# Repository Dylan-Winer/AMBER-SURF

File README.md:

# AMBER-SURF
Repository hosting project files as part of my Summer Undergraduate Research Fellowship (SURF) 2025 project within the AMBER Lab at Caltech.

## Mechanical Components & Assembly

This section covers the physical build of the foot modules and begins exactly where the right-foot assembly was left off.

---

### Complete the Right Foot: Rubber Sole & Adhesive Nuts

1. **Get the sole DXF**
   - Download `sole_base.DXF` from this repo:  
     https://github.com/Dylan-Winer/AMBER-SURF/blob/main/SolidWorks-CAD/G1_Integration/DXF_G1_3/sole_base.DXF

2. **Cut the rubber sole**
   - Acquire **1/8" thick rubber** sheet.
   - **Waterjet** cut the sole using `sole_base.DXF`. Deburr/trim if needed for a clean perimeter.

3. **Bolt the remaining hardware**
   - From the bag labeled **“4/40 BOLTS & SPACERS”**, locate the **four remaining adhesive nuts**, **4-40 bolts**, and **spacers**.
   - Install these in the positions on the **right foot** where bolts are currently missing. Snug the 4-40 bolts; don’t over-torque.
   - There are through-holes cut into the cable channels on both the heel connectors. Use these to fit an allen key through. You may need to push the cables out of the way with the allen key.

4. **Bond the adhesive nuts to the rubber**
   - Remove the rubber sole; place a small, even bead of **Gorilla Glue** *or* a suitable **epoxy** on the **underside of all 8 adhesive nuts**.
   - Press the **waterjet rubber sole** onto the adhesive nuts with **even pressure**. Using a **vise** to hold the foot makes this easier; protect surfaces with scrap pads.
   - **Cure per adhesive instructions.** (If using Gorilla Glue, lightly dampen the rubber for proper foaming; for epoxy, degrease both surfaces first.)

5. **Prep for base plate + toe installation**
   - **Unscrew** the four **4-40 bolts & spacers** that mount the **heel connector** to the foot so the **right foot matches the left**.
   - The **heel must come off** so the **base plate and toe** can be **slid on from the front**.

> ✅ Quick checklist  
> - [ ] Rubber sole waterjet and is clean  
> - [ ] All 8 adhesive nuts bonded and cured  
> - [ ] Heel connector hardware removed (right foot)  
> - [ ] Fit check: base plate + toe can slide on from the front

---

### Install Each Module (Left & Right Feet)

1. **Slide-on fit**
   - **Slip the G1 foot** through the **toe cover** until the bottom of the G1 foot is **fully seated** on the **top of the bottom base plate**.
   - Verify the **toe and heel bumpers** **fully enclose** the foot with uniform contact.

2. **Reinstall heel hardware**
   - Cover the heel of the G1 with the **heel mounts**.
   - **Screw the four 4-40 bolts + spacers** into the **four heel-mount holes**. Tighten evenly in a cross pattern until snug.

3. **Cable & strain relief**
   - Route cables cleanly along edges and through any provided channels. Add **strain relief** (zip ties/adhesive anchors) to protect connectors and solder joints.

4. **USB to host**
   - Connect **micro-USB** from **each foot module** to the computer. In practice you’ll likely use **USB extension cables** plus **90° micro-USB cables** to keep a low profile.

5. **Proceed to logging**
   - Follow the **Arduino/CoolTerm** instructions in the previous section to set **per-foot baud rates** and **capture data**.

# AMBER Lab SURF 2025 — G1 Foot Sensing Module

High-rate (1000 Hz) force + IMU logging for the Unitree G1 humanoid foot.  
The following contains Teensy 4.1 usage notes to capture synchronized FSR forces and MPU-6050 orientation/gyro data to CSV via CoolTerm.

---

## TL;DR (How to run & log)

1. **Install & open CoolTerm.**
2. **Connect the Teensy (USB).**
3. In CoolTerm: **Connection → Options…**
   - **Port:** select the COM port associated with your Teensy.
   - **Baudrate:** set to the same value used in firmware `Serial.begin(BAUDRATE)` (defaults shown in the code below are `2,000,000`).
   - Click **OK**.
4. Click **Connect**.
5. Start file logging: **Connection → File Capture → Start…**
   - Choose a folder, **create/name a `.txt` file**, click **Save**.
6. In the CoolTerm terminal, press **`s`** to **start** the program (CSV header prints once).
7. **Run your G1 test** (walk/stance as needed).
8. Press **`x`** to **stop** the program.
9. Stop file logging: **Connection → File Capture → Stop**.

> **Left vs Right foot**  
> You will run **two Teensies** (left/right) at **different baud rates** to avoid USB bandwidth contention and to keep ports distinct.  
> - Edit `Serial.begin(BAUDRATE)` in each foot’s firmware (e.g., Left `2,000,000`, Right `1,500,000`).  
> - In CoolTerm, pick the matching COM port and set the **Baudrate** accordingly for each run.

---

## Data format (CSV columns)

When logging is active, the firmware prints:
time_s,FSR1_N,FSR2_N,FSR3_N,FSR4_N,qw,qx,qy,qz,gx_rad_s,gy_rad_s,gz_rad_s

- **time_s** — seconds since you pressed `s`
- **FSR*_N** — force in Newtons after per-sensor linear calibration and dead-zone/zero-clipping (<2 N → 0)
- **qw..qz** — unit quaternion from Mahony filter
- **g*_rad_s** — body-frame gyro rates (rad/s) derived from RAW with offsets & scale

---

## Hardware overview

- **Controller:** Teensy 4.1 (3.3 V logic)
- **FSRs:** 4× FlexiForce A201 (per-sensor linear calibration applied)
- **IMU:** MPU-6050
- **Loop rate:** 1000 Hz fixed tick (1 ms)

---

## Build & Flash (Teensy 4.x)

1. Open this repo’s firmware in **Arduino IDE** or **Arduino CLI** with **Teensyduino** installed.
2. Select **Board: Teensy 4.0/4.1** and the correct **Port**.
3. (Optional) Adjust:
   - `Serial.begin(BAUDRATE)` for your left/right feet.
   - FSR calibration `slope[]` and `intercept[]`.
   - Mahony gains `Kp`, `Ki`.
4. **Upload**.

## 3) Analyze Data (Python)

Program link (full script):  
**➡️ https://github.com/Dylan-Winer/AMBER-SURF/blob/main/Python_Code/G1_Data_Analysis/Force_Plot_Final.py**

**Use it like this:**
- Replace `file_path` with your CoolTerm **.txt/.csv** path.
- Set `t_start_s` and `t_end_s` (easiest way to focus on a window; set `0` to analyze everything).
- Run the script to get **plots** and **replay videos** (MP4 if FFmpeg available; otherwise GIF).
- Don’t need outputs? Comment out the plot sections and/or the `make_replay_video(...)` calls.

**Expected columns** in the file:
time_s,FSR1_N,FSR2_N,FSR3_N,FSR4_N,qw,qx,qy,qz,gx_rad_s,gy_rad_s,gz_rad_s

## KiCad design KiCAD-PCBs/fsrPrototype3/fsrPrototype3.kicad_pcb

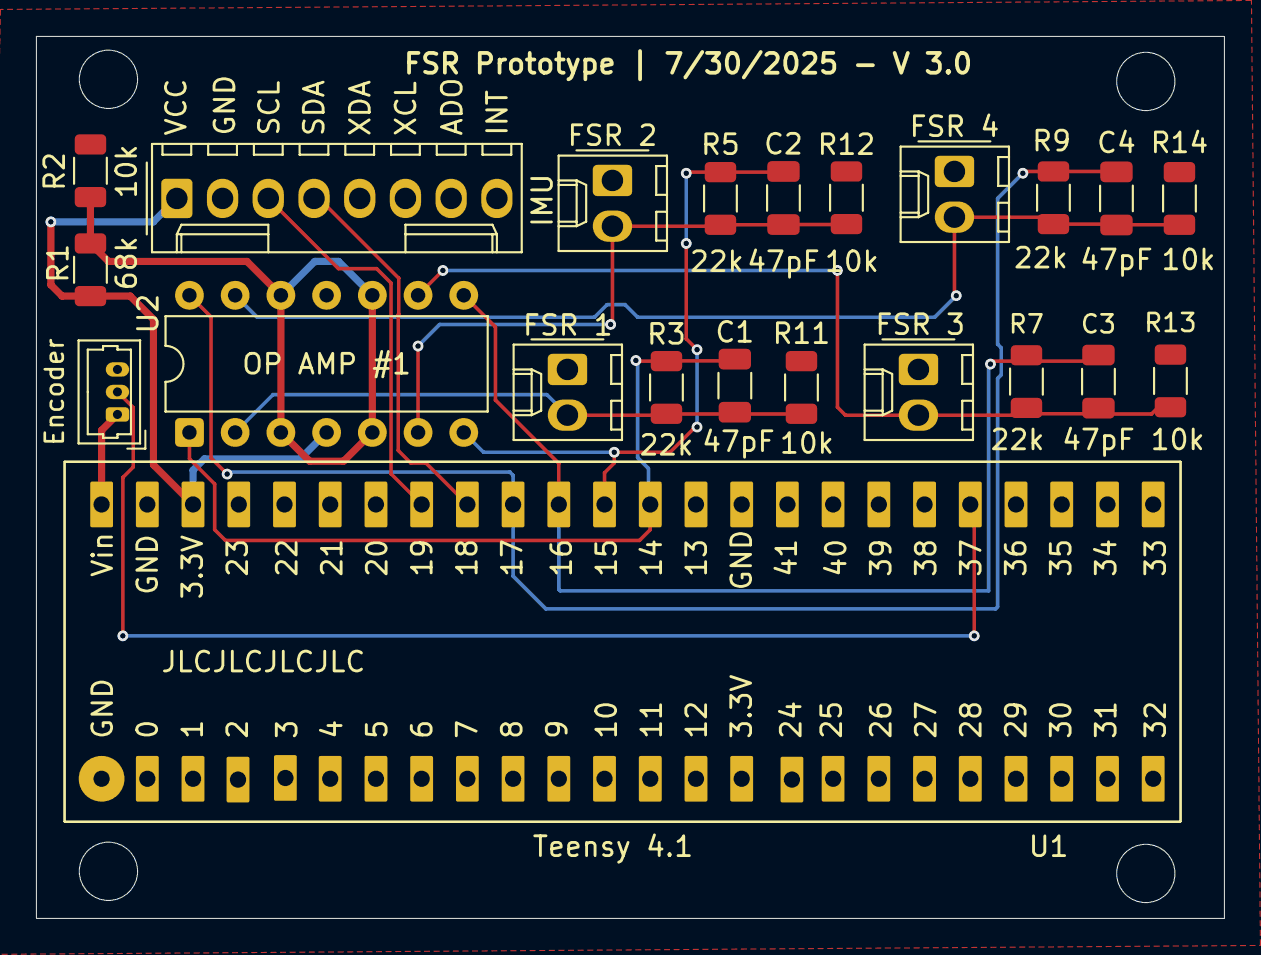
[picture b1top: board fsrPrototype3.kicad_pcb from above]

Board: 2 copper layers, 66.0 x 49.0 mm, 22 parts (0 on the bottom side), 15 nets.

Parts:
C1, C2, C3, C4: 47pF; C_1206_3216Metric
Encoder: Conn_01x03; Molex_PicoBlade_53047-0310_1x03_P1.25mm_Vertical
FSR 1: FSR_1_Conn; Molex_KK-254_AE-6410-02A_1x02_P2.54mm_Vertical
FSR 2: FSR_2_Conn; Molex_KK-254_AE-6410-02A_1x02_P2.54mm_Vertical
FSR 3: FSR_3_Conn; Molex_KK-254_AE-6410-02A_1x02_P2.54mm_Vertical
FSR 4: FSR_4_Conn; Molex_KK-254_AE-6410-02A_1x02_P2.54mm_Vertical
IMU: Conn_01x08; Molex_KK-254_AE-6410-08A_1x08_P2.54mm_Vertical
R1: 68k; R_1206_3216Metric
R2, R11, R12, R13, R14: 10k; R_1206_3216Metric
R3, R5, R7, R9: 22k; R_1206_3216Metric
U1: Teensy4.1; Teensy_4.1
U2: MCP6004; DIP-14_W7.62mm

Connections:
GND: Encoder.3, FSR 1.1, FSR 2.1, FSR 3.1, FSR 4.1, IMU.2, R2.2, R11.1, R12.1, R13.1, R14.1, U1.1 (GND), U2.11 (V-)
unnamed: C1.1, FSR 1.2, R3.1, R11.2, U2.2 (-)
unnamed: C2.1, FSR 2.2, R5.1, R12.2, U2.6 (-)
unnamed: C3.1, FSR 3.2, R7.1, R13.2, U2.9 (-)
unnamed: C4.1, FSR 4.2, R9.1, R14.2, U2.13 (-)
unnamed: IMU.1, R1.1, U1.46 (3V3), U2.4 (V+)
unnamed: IMU.3, U1.41 (19_A5_SCL)
unnamed: IMU.4, U1.40 (18_A4_SDA)
unnamed: Encoder.1, U1.48 (VIN)
unnamed: Encoder.2, U1.29 (37_CS)
unnamed: C1.2, R3.2, U1.36 (14_A0_TX3_SPDIF_OUT), U2.1
unnamed: C2.2, R5.2, U1.37 (15_A1_RX3_SPDIF_IN), U2.7
unnamed: C3.2, R7.2, U1.38 (16_A2_RX4_SCL1), U2.8
unnamed: C4.2, R9.2, U1.39 (17_A3_TX4_SDA1), U2.14
unnamed: R1.2, R2.1, U2.3 (+), U2.5 (+), U2.10 (+), U2.12 (+)

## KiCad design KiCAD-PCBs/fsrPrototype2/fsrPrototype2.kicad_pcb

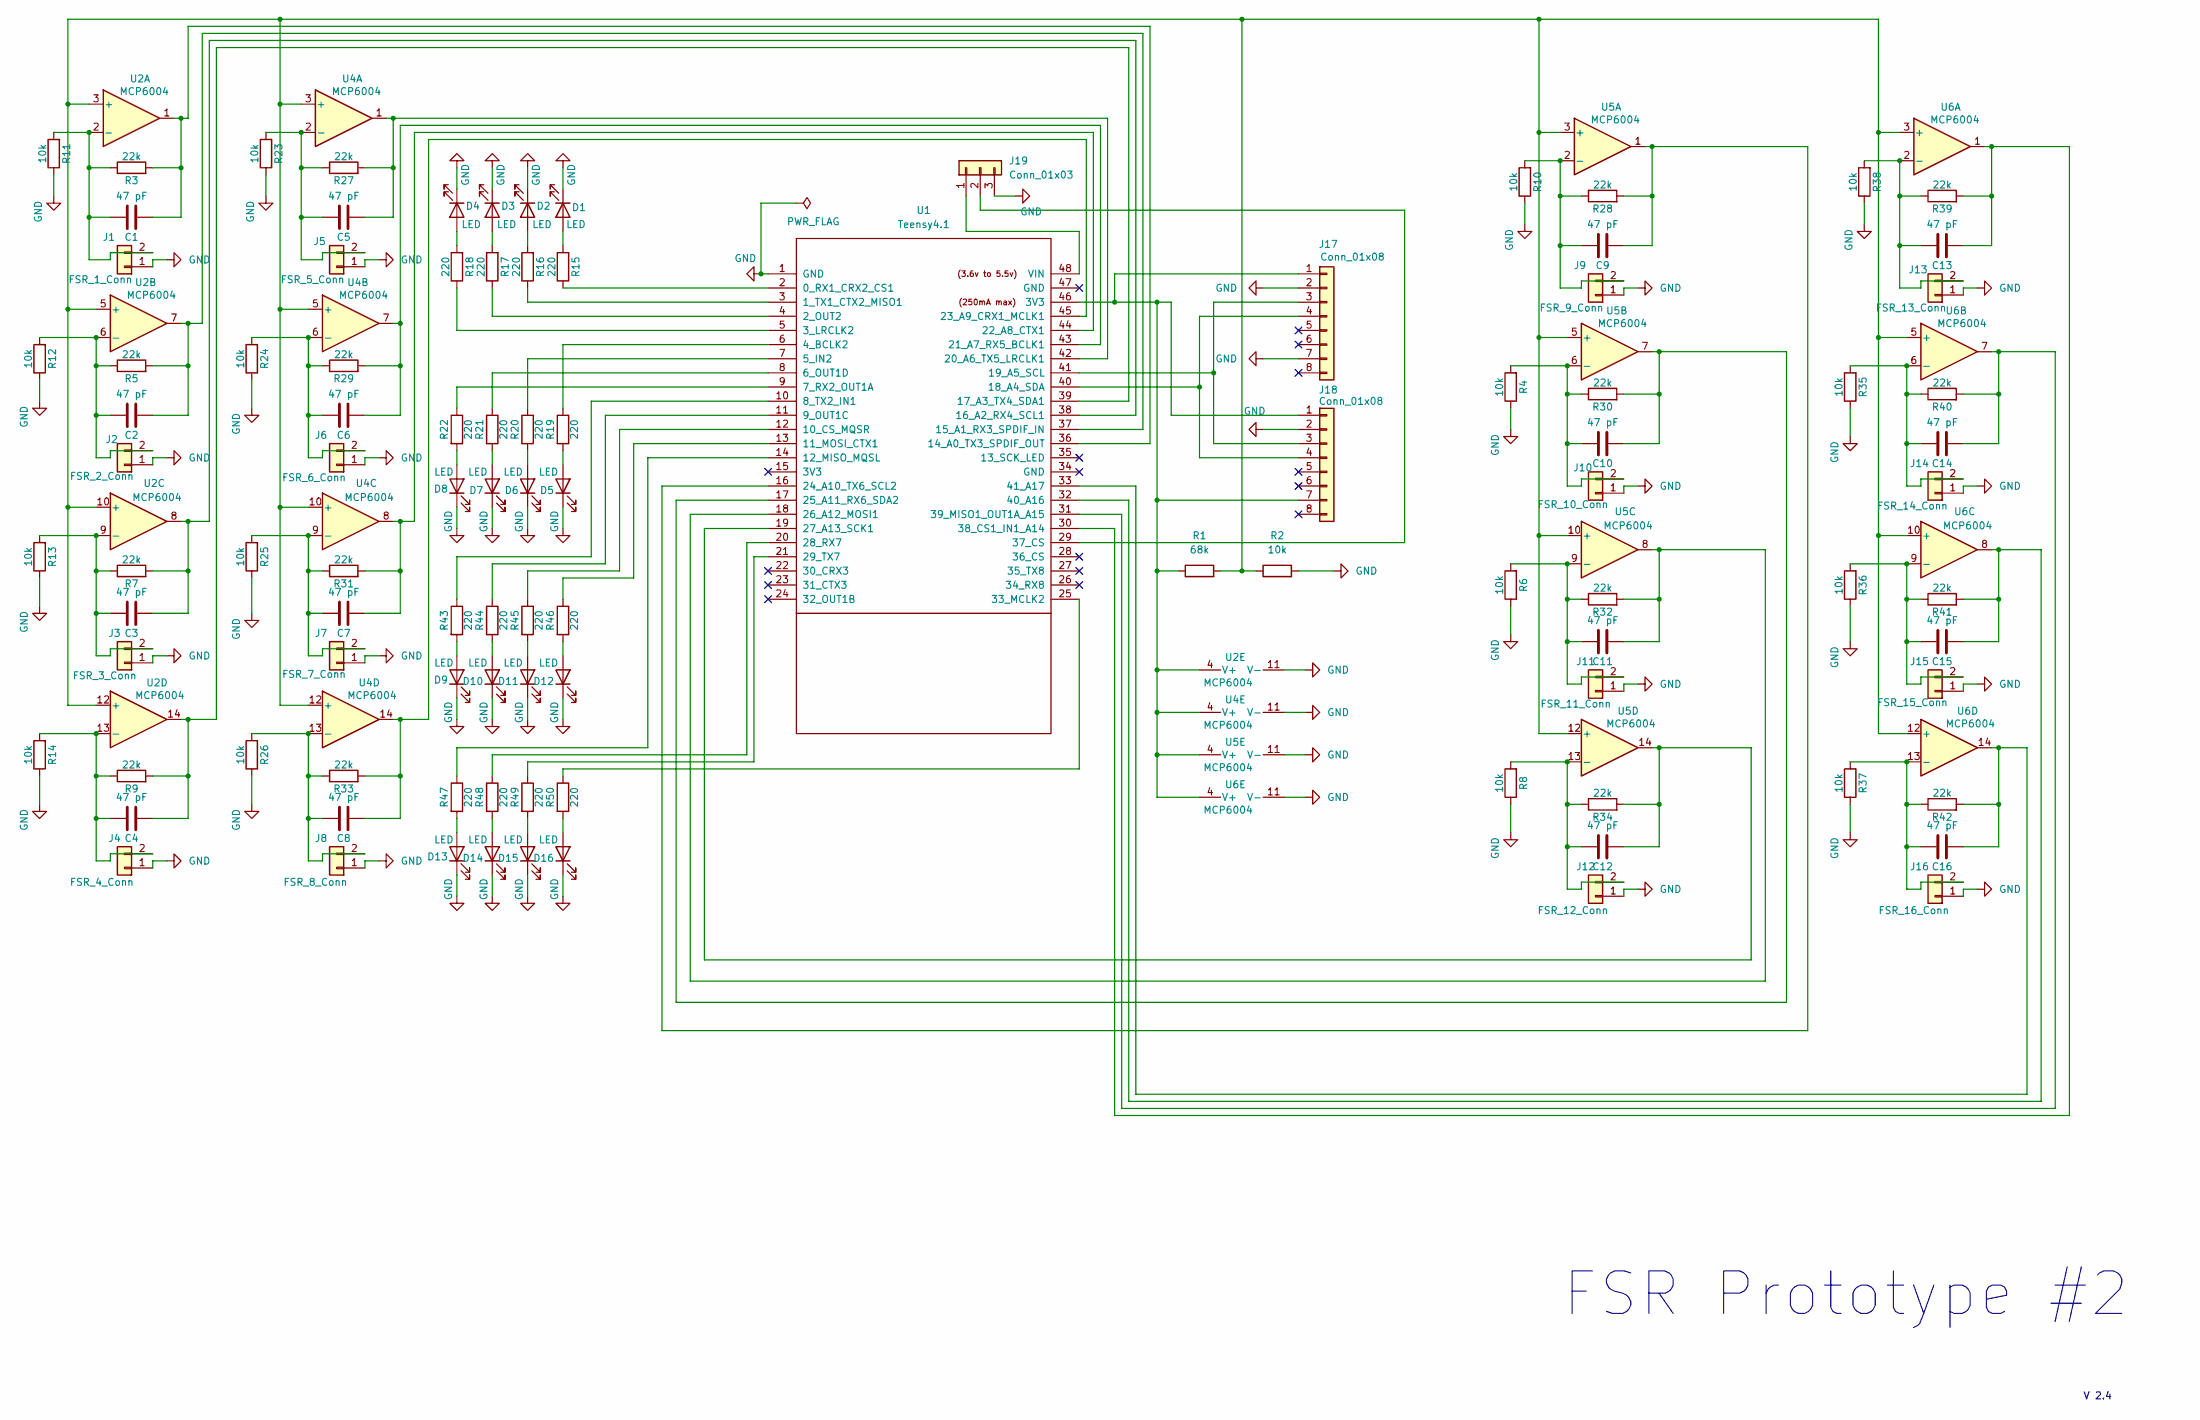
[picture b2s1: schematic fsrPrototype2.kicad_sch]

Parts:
C1, C2, C3, C4, C5, C6, C7, C8, C9, C10, C11, C12, C13, C14, C15, C16: 47 pF; C_1206_3216Metric
D1, D2, D3, D4, D5, D6, D7, D8, D9, D10, D11, D12, D13, D14, D15, D16: LED; LED_1206_3216Metric
J1: FSR_1_Conn; Molex_KK-254_AE-6410-02A_1x02_P2.54mm_Vertical
J2: FSR_2_Conn; Molex_KK-254_AE-6410-02A_1x02_P2.54mm_Vertical
J3: FSR_3_Conn; Molex_KK-254_AE-6410-02A_1x02_P2.54mm_Vertical
J4: FSR_4_Conn; Molex_KK-254_AE-6410-02A_1x02_P2.54mm_Vertical
J5: FSR_5_Conn; Molex_KK-254_AE-6410-02A_1x02_P2.54mm_Vertical
J6: FSR_6_Conn; Molex_KK-254_AE-6410-02A_1x02_P2.54mm_Vertical
J7: FSR_7_Conn; Molex_KK-254_AE-6410-02A_1x02_P2.54mm_Vertical
J8: FSR_8_Conn; Molex_KK-254_AE-6410-02A_1x02_P2.54mm_Vertical
J9: FSR_9_Conn; Molex_KK-254_AE-6410-02A_1x02_P2.54mm_Vertical
J10: FSR_10_Conn; Molex_KK-254_AE-6410-02A_1x02_P2.54mm_Vertical
J11: FSR_11_Conn; Molex_KK-254_AE-6410-02A_1x02_P2.54mm_Vertical
J12: FSR_12_Conn; Molex_KK-254_AE-6410-02A_1x02_P2.54mm_Vertical
J13: FSR_13_Conn; Molex_KK-254_AE-6410-02A_1x02_P2.54mm_Vertical
J14: FSR_14_Conn; Molex_KK-254_AE-6410-02A_1x02_P2.54mm_Vertical
J15: FSR_15_Conn; Molex_KK-254_AE-6410-02A_1x02_P2.54mm_Vertical
J16: FSR_16_Conn; Molex_KK-254_AE-6410-02A_1x02_P2.54mm_Vertical
J17, J18: Conn_01x08; Molex_KK-254_AE-6410-08A_1x08_P2.54mm_Vertical
J19: Conn_01x03; Molex_PicoBlade_53047-0310_1x03_P1.25mm_Vertical
R1: 68k; R_1206_3216Metric
R2, R4, R6, R8, R10, R11, R12, R13, R14, R23, R24, R25, R26, R35, R36, R37, R38: 10k; R_1206_3216Metric
R3, R5, R7, R9, R27, R28, R29, R30, R31, R32, R33, R34, R39, R40, R41, R42: 22k; R_1206_3216Metric
R15, R16, R17, R18, R19, R20, R21, R22, R43, R44, R45, R46, R47, R48, R49, R50: 220; R_1206_3216Metric
U1: Teensy4.1; Teensy_4.1
U2, U4, U5, U6: MCP6004; DIP-14_W7.62mm

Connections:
GND: D1.1 (K), D2.1 (K), D3.1 (K), D4.1 (K), D5.1 (K), D6.1 (K), D7.1 (K), D8.1 (K), D9.1 (K), D10.1 (K), D11.1 (K), D12.1 (K), D13.1 (K), D14.1 (K), D15.1 (K), D16.1 (K), J1.1, J2.1, J3.1, J4.1, J5.1, J6.1, J7.1, J8.1, J9.1, J10.1, J11.1, J12.1, J13.1, J14.1, J15.1, J16.1, J17.2, J17.7, J18.2, J19.3, R2.2, R4.1, R6.1, R8.1, R10.1, R11.1, R12.1, R13.1, R14.1, R23.1, R24.1, R25.1, R26.1, R35.1, R36.1, R37.1, R38.1, U1.1 (GND), U2.11 (V-), U4.11 (V-), U5.11 (V-), U6.11 (V-); also elsewhere on the board
unnamed: D1.2 (A), R15.2
unnamed: D2.2 (A), R16.2
unnamed: D3.2 (A), R17.2
unnamed: D4.2 (A), R18.2
unnamed: D5.2 (A), R19.2
unnamed: D6.2 (A), R20.2
unnamed: D7.2 (A), R21.2
unnamed: D8.2 (A), R22.2
unnamed: D9.2 (A), R43.2
unnamed: D10.2 (A), R44.2
unnamed: D11.2 (A), R45.2
unnamed: D12.2 (A), R46.2
unnamed: D13.2 (A), R47.2
unnamed: D14.2 (A), R48.2
unnamed: D15.2 (A), R49.2
unnamed: D16.2 (A), R50.2
unnamed: C1.1, J1.2, R3.1, R11.2, U2.2 (-)
unnamed: C2.1, J2.2, R5.1, R12.2, U2.6 (-)
unnamed: C3.1, J3.2, R7.1, R13.2, U2.9 (-)
unnamed: C4.1, J4.2, R9.1, R14.2, U2.13 (-)
unnamed: C5.1, J5.2, R23.2, R27.1, U4.2 (-)
unnamed: C6.1, J6.2, R24.2, R29.1, U4.6 (-)
unnamed: C7.1, J7.2, R25.2, R31.1, U4.9 (-)
unnamed: C8.1, J8.2, R26.2, R33.1, U4.13 (-)
unnamed: C9.1, J9.2, R10.2, R28.1, U5.2 (-)
unnamed: C10.1, J10.2, R4.2, R30.1, U5.6 (-)
unnamed: C11.1, J11.2, R6.2, R32.1, U5.9 (-)
unnamed: C12.1, J12.2, R8.2, R34.1, U5.13 (-)
unnamed: C13.1, J13.2, R38.2, R39.1, U6.2 (-)
unnamed: C14.1, J14.2, R35.2, R40.1, U6.6 (-)
unnamed: C15.1, J15.2, R36.2, R41.1, U6.9 (-)
unnamed: C16.1, J16.2, R37.2, R42.1, U6.13 (-)
unnamed 33: J17.1, J18.1, J18.7, R1.1, U1.46 (3V3), U2.4 (V+), U4.4 (V+), U5.4 (V+), U6.4 (V+); also elsewhere on the board
unnamed: J17.3, J18.3, U1.41 (19_A5_SCL)
unnamed: J17.4, J18.4, U1.40 (18_A4_SDA)
unnamed: J19.1, U1.48 (VIN)
unnamed: J19.2, U1.29 (37_CS)
unnamed: R15.1, U1.2 (0_RX1_CRX2_CS1)
unnamed: R16.1, U1.3 (1_TX1_CTX2_MISO1)
unnamed: R17.1, U1.4 (2_OUT2)
unnamed: R18.1, U1.5 (3_LRCLK2)
unnamed: R19.1, U1.6 (4_BCLK2)
unnamed: R20.1, U1.7 (5_IN2)
unnamed: R21.1, U1.8 (6_OUT1D)
unnamed: R22.1, U1.9 (7_RX2_OUT1A)
unnamed: R43.1, U1.10 (8_TX2_IN1)
unnamed: R44.1, U1.11 (9_OUT1C)
unnamed: R45.1, U1.12 (10_CS_MQSR)
unnamed: R46.1, U1.13 (11_MOSI_CTX1)
unnamed: R47.1, U1.14 (12_MISO_MQSL)
unnamed: C1.2, R3.2, U1.36 (14_A0_TX3_SPDIF_OUT), U2.1
unnamed: C2.2, R5.2, U1.37 (15_A1_RX3_SPDIF_IN), U2.7
unnamed: C3.2, R7.2, U1.38 (16_A2_RX4_SCL1), U2.8
unnamed: C4.2, R9.2, U1.39 (17_A3_TX4_SDA1), U2.14
unnamed: C5.2, R27.2, U1.42 (20_A6_TX5_LRCLK1), U4.1
unnamed: C6.2, R29.2, U1.43 (21_A7_RX5_BCLK1), U4.7
unnamed: C7.2, R31.2, U1.44 (22_A8_CTX1), U4.8
unnamed: C8.2, R33.2, U1.45 (23_A9_CRX1_MCLK1), U4.14
unnamed: C9.2, R28.2, U1.16 (24_A10_TX6_SCL2), U5.1
unnamed: C10.2, R30.2, U1.17 (25_A11_RX6_SDA2), U5.7
unnamed: C11.2, R32.2, U1.18 (26_A12_MOSI1), U5.8
unnamed: C12.2, R34.2, U1.19 (27_A13_SCK1), U5.14
unnamed: R48.1, U1.20 (28_RX7)
unnamed: R49.1, U1.21 (29_TX7)
unnamed: R50.1, U1.25 (33_MCLK2)
unnamed: C13.2, R39.2, U1.30 (38_CS1_IN1_A14), U6.1
unnamed: C14.2, R40.2, U1.31 (39_MISO1_OUT1A_A15), U6.7
unnamed: C15.2, R41.2, U1.32 (40_A16), U6.8
unnamed: C16.2, R42.2, U1.33 (41_A17), U6.14
unnamed 70: R1.2, R2.1, U2.3 (+), U2.5 (+), U2.10 (+), U2.12 (+), U4.3 (+), U4.5 (+), U4.10 (+), U4.12 (+), U5.3 (+), U5.5 (+), U5.10 (+), U5.12 (+), U6.3 (+), U6.5 (+), U6.10 (+), U6.12 (+); also elsewhere on the board

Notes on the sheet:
FSR Prototype #2
V 2.4

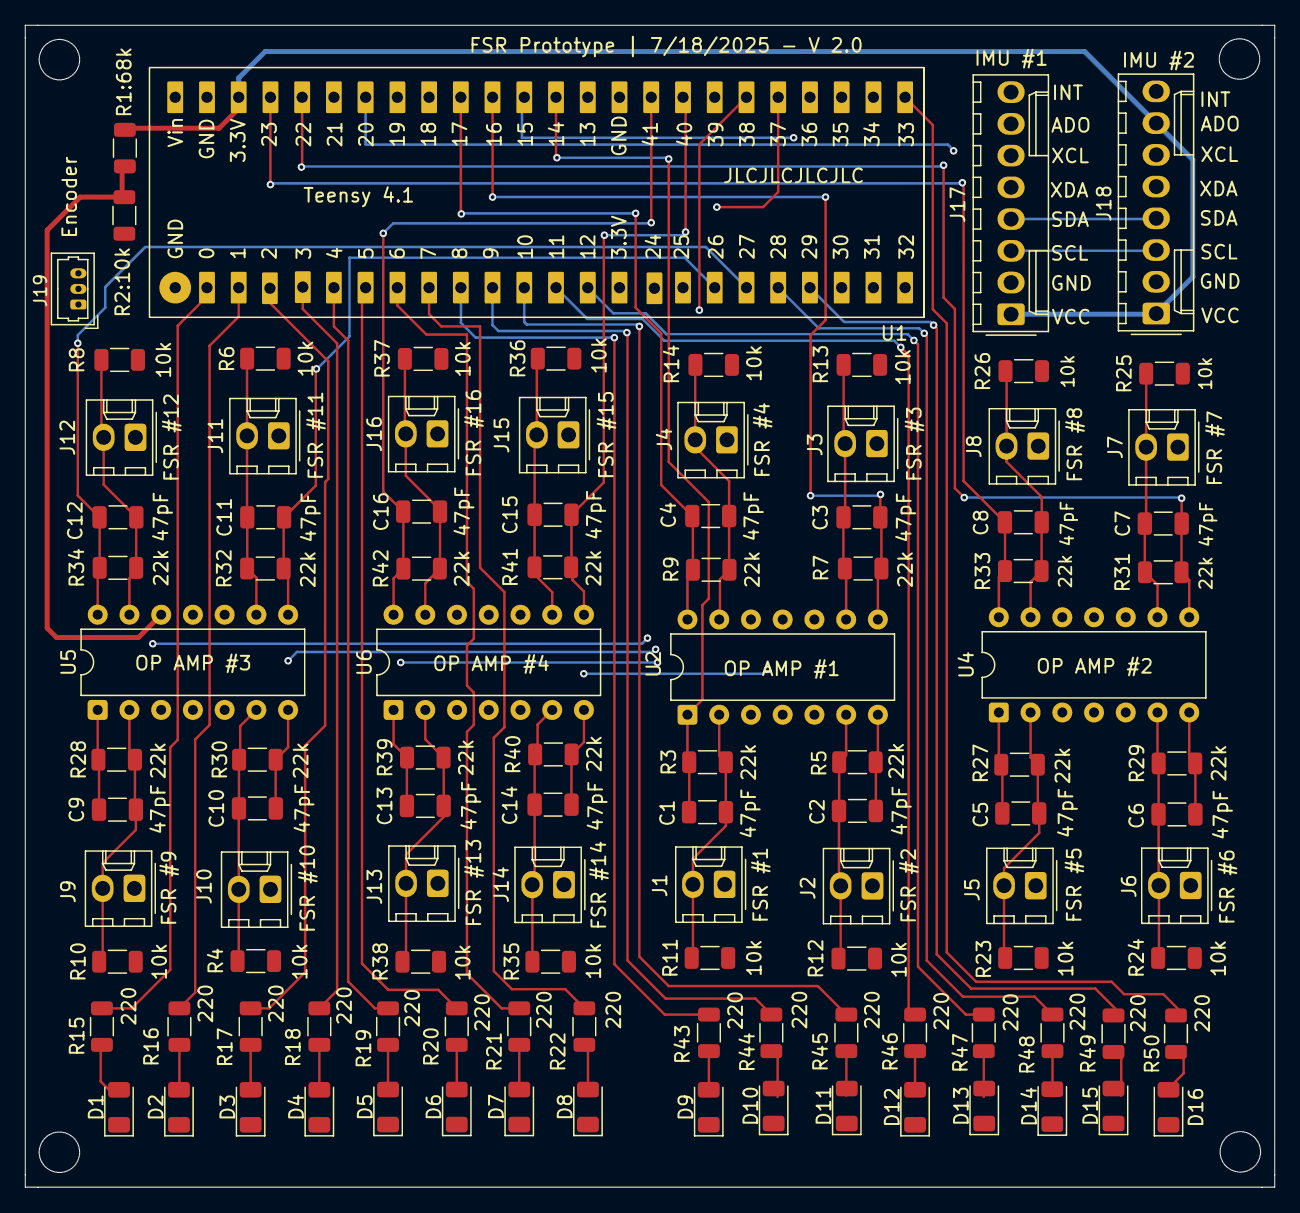
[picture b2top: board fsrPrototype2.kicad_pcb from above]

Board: 4 copper layers, 100.0 x 93.0 mm, 106 parts (0 on the bottom side), 71 nets.

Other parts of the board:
R1:68k: 68k; R_1206_3216Metric
R2:10k: 10k; R_1206_3216Metric

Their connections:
GND: R2:10k.2; also elsewhere on the board
unnamed 33: R1:68k.1; also elsewhere on the board
unnamed 70: R1:68k.2, R2:10k.1; also elsewhere on the board

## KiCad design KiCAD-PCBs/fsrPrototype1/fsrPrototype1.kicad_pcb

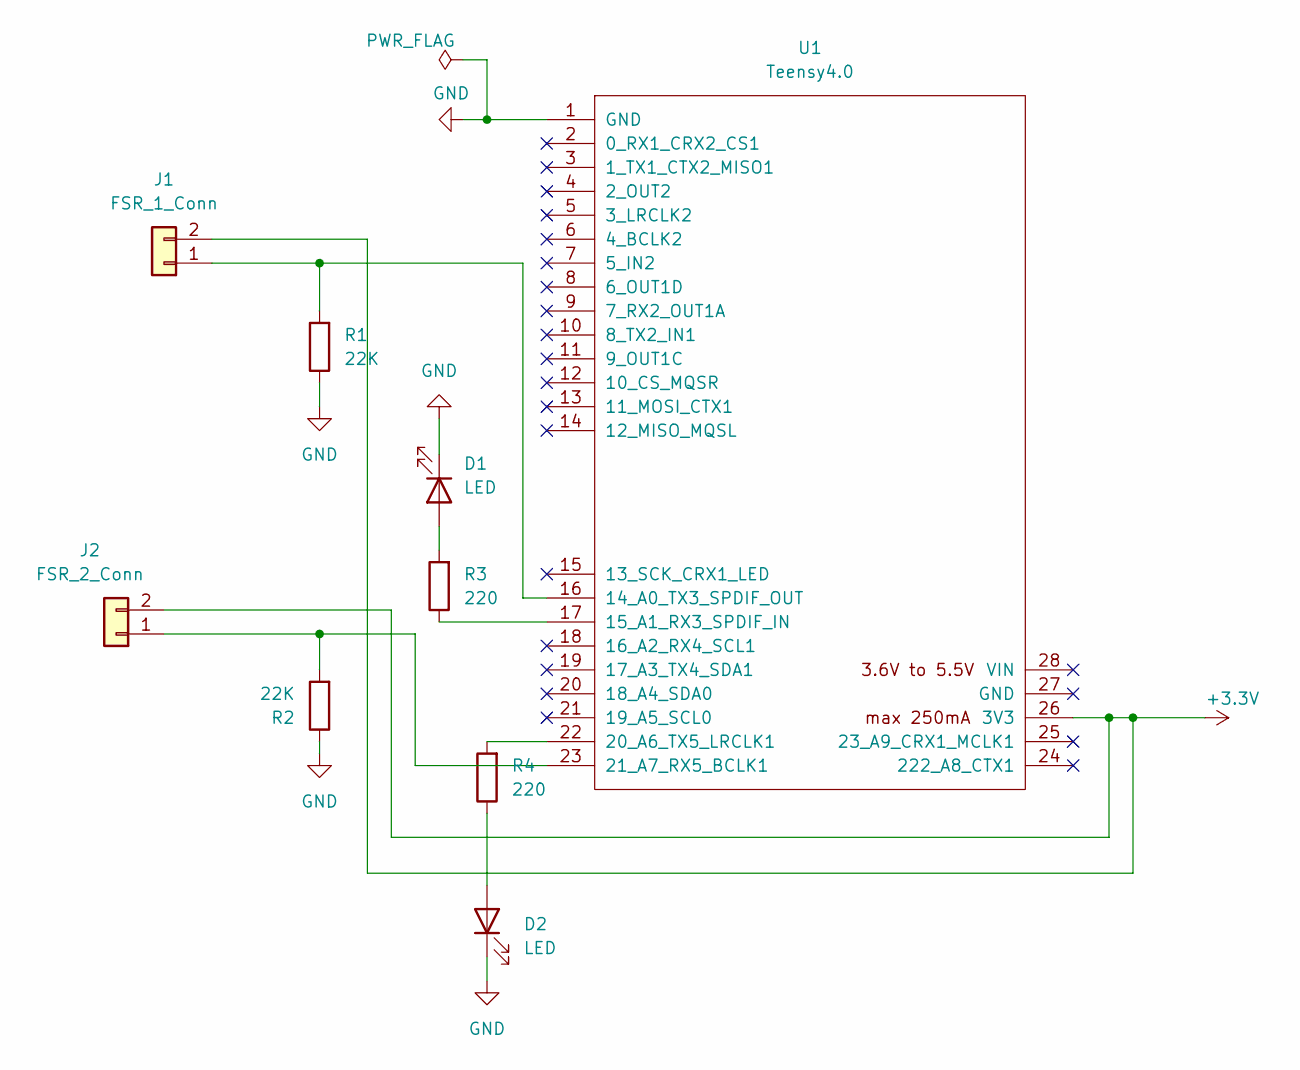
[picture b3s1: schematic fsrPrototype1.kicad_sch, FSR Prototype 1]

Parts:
D1, D2: LED; LED_1206_3216Metric
J1: FSR_1_Conn; Molex_KK-254_AE-6410-02A_1x02_P2.54mm_Vertical
J2: FSR_2_Conn; Molex_KK-254_AE-6410-02A_1x02_P2.54mm_Vertical
R1, R2: 22K; R_1206_3216Metric
R3, R4: 220; R_1206_3216Metric
U1: Teensy4.0; Teensy_4.0_Socketed

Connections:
+3.3V: J1.2, J2.2, U1.26 (3V3)
GND: D1.1 (K), D2.1 (K), R1.1, R2.1, U1.1 (GND)
unnamed: D1.2 (A), R3.2
unnamed: D2.2 (A), R4.1
unnamed: J1.1, R1.2, U1.16 (14_A0_TX3_SPDIF_OUT)
unnamed: J2.1, R2.2, U1.23 (21_A7_RX5_BCLK1)
unnamed: R3.1, U1.17 (15_A1_RX3_SPDIF_IN)
unnamed: R4.2, U1.22 (20_A6_TX5_LRCLK1)

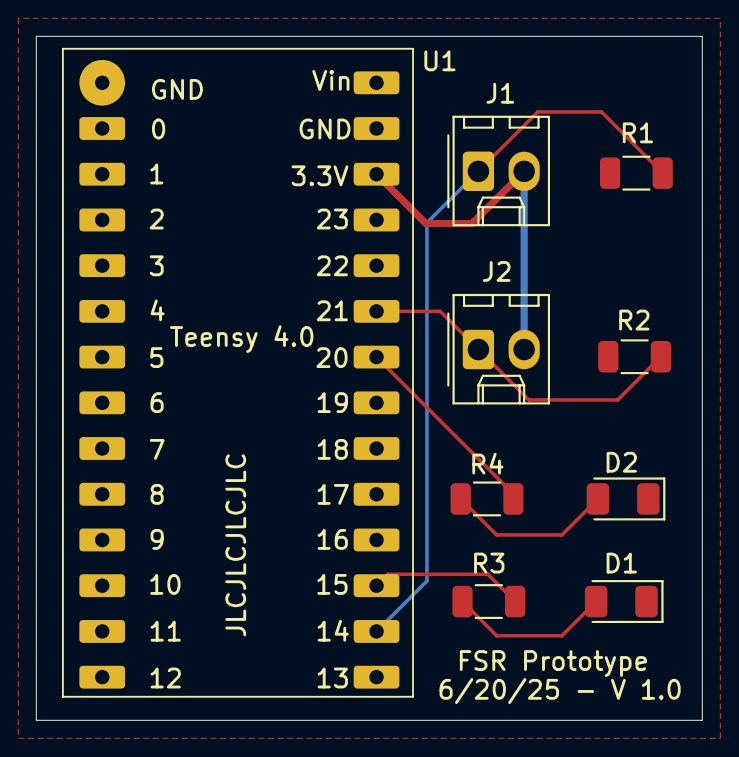
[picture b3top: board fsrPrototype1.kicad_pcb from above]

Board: 2 copper layers, 37.0 x 38.0 mm, 9 parts (0 on the bottom side), 8 nets.

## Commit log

2025-07-29 Add files via upload
    initial CAD prototype for sandwich structure
2025-07-29 Add files via upload
    Passive toe mechanism version 1 CAD
2025-07-29 Add files via upload
    Passive toe mechanism V2 with integrated sensors CAD
2025-07-29 Add files via upload
    Initial CAD for integrating sensors onto G1 humanoid foot
2025-07-29 PCB Prototype V1
    KiCAD / Gerber files for initial PCB with 2 FSRs, 2 LEDs, and a Teensy 4.0
2025-07-29 PCB Prototype 2
    KiCAD / Gerber files for PCB prototype 2 with 4 op amps, 16 FSRs, 16 LEDs, encoder, 2 IMUs, and a Teensy 4.1
2025-07-29 Python code for calibration
    Python scripts & notebooks to calibrate sensors and analyze their data
2025-07-29 Created hierarchical folders
2025-08-15 updated project files from SURF
